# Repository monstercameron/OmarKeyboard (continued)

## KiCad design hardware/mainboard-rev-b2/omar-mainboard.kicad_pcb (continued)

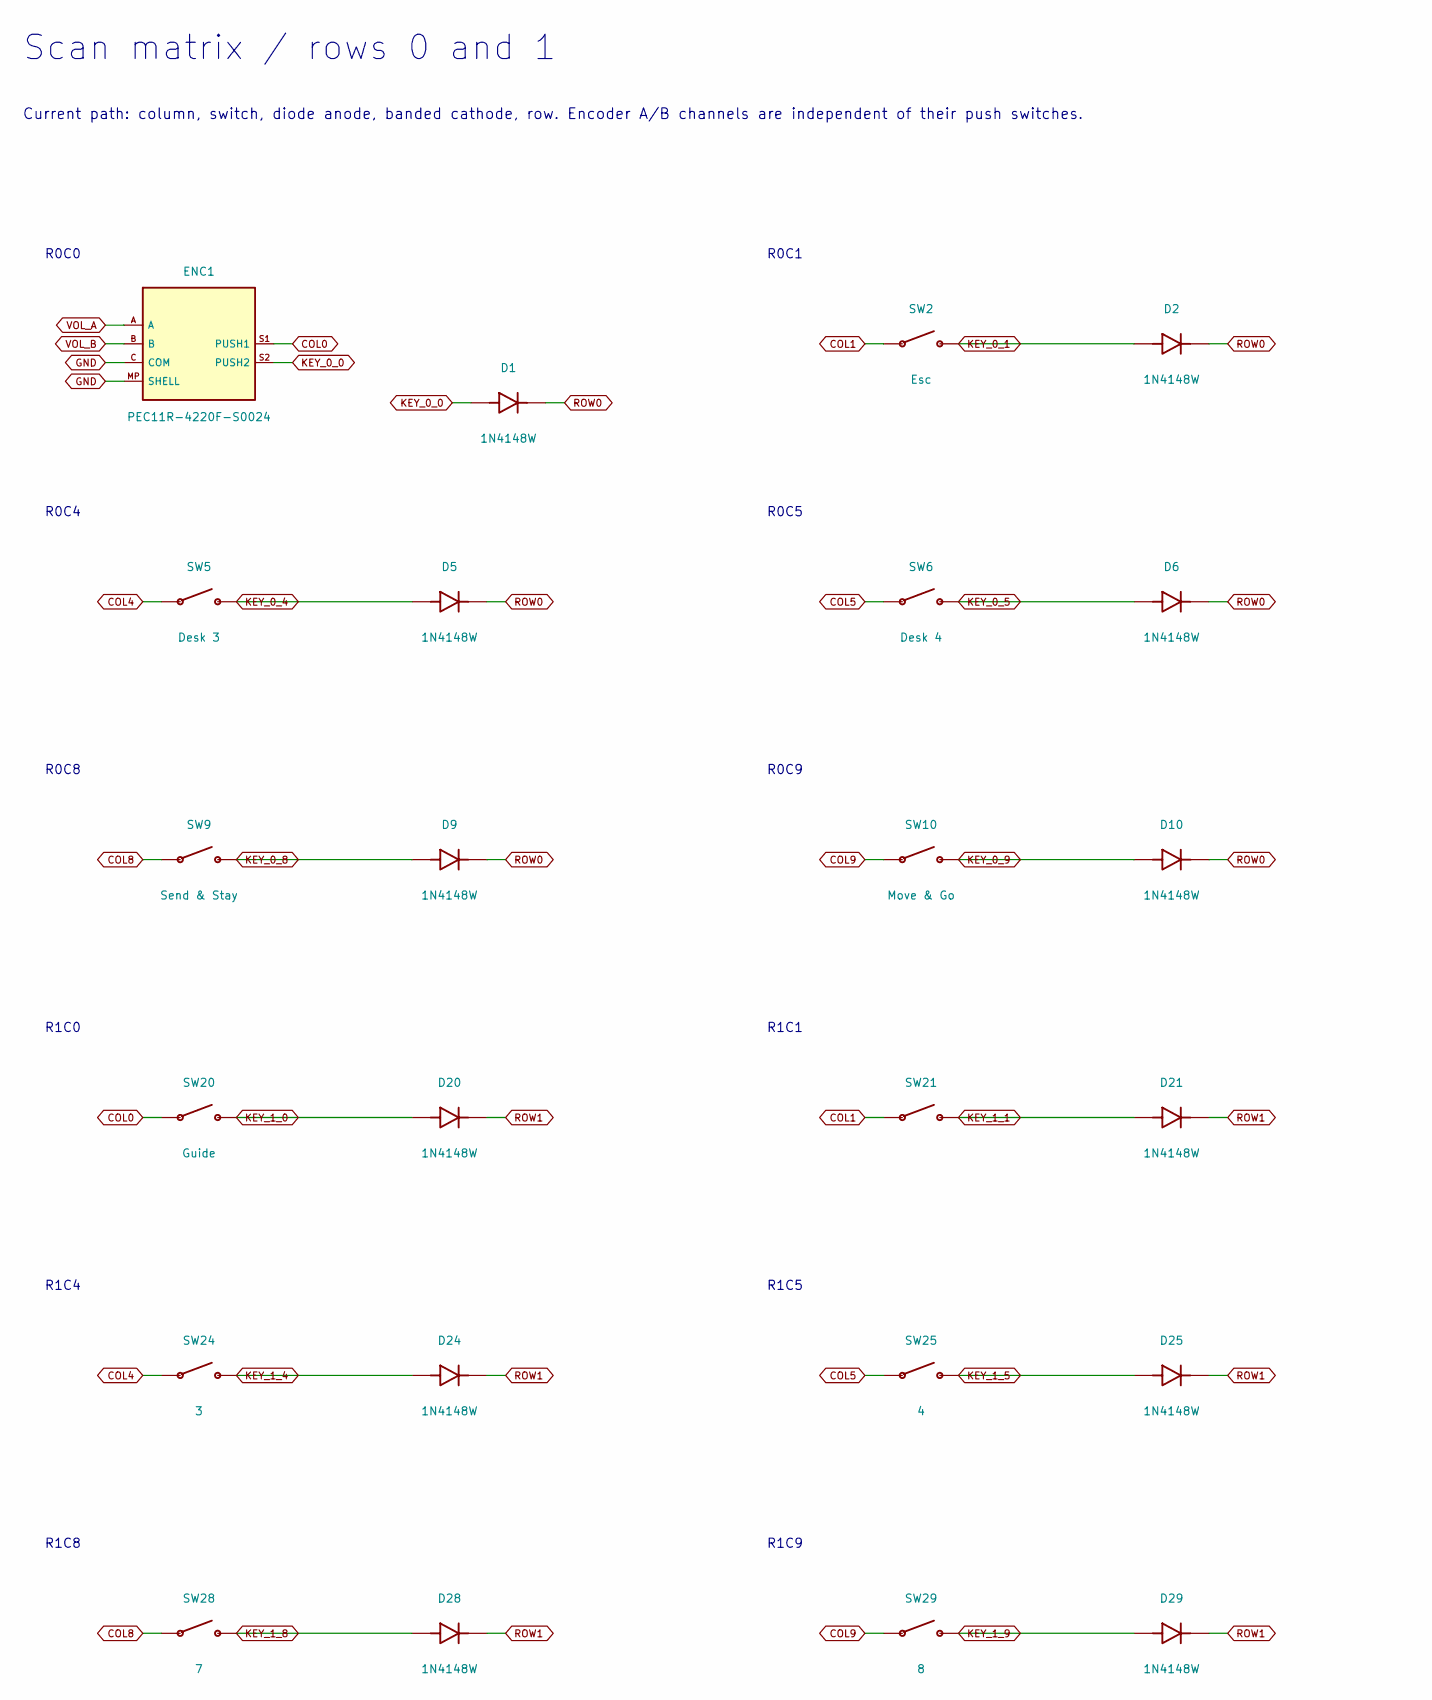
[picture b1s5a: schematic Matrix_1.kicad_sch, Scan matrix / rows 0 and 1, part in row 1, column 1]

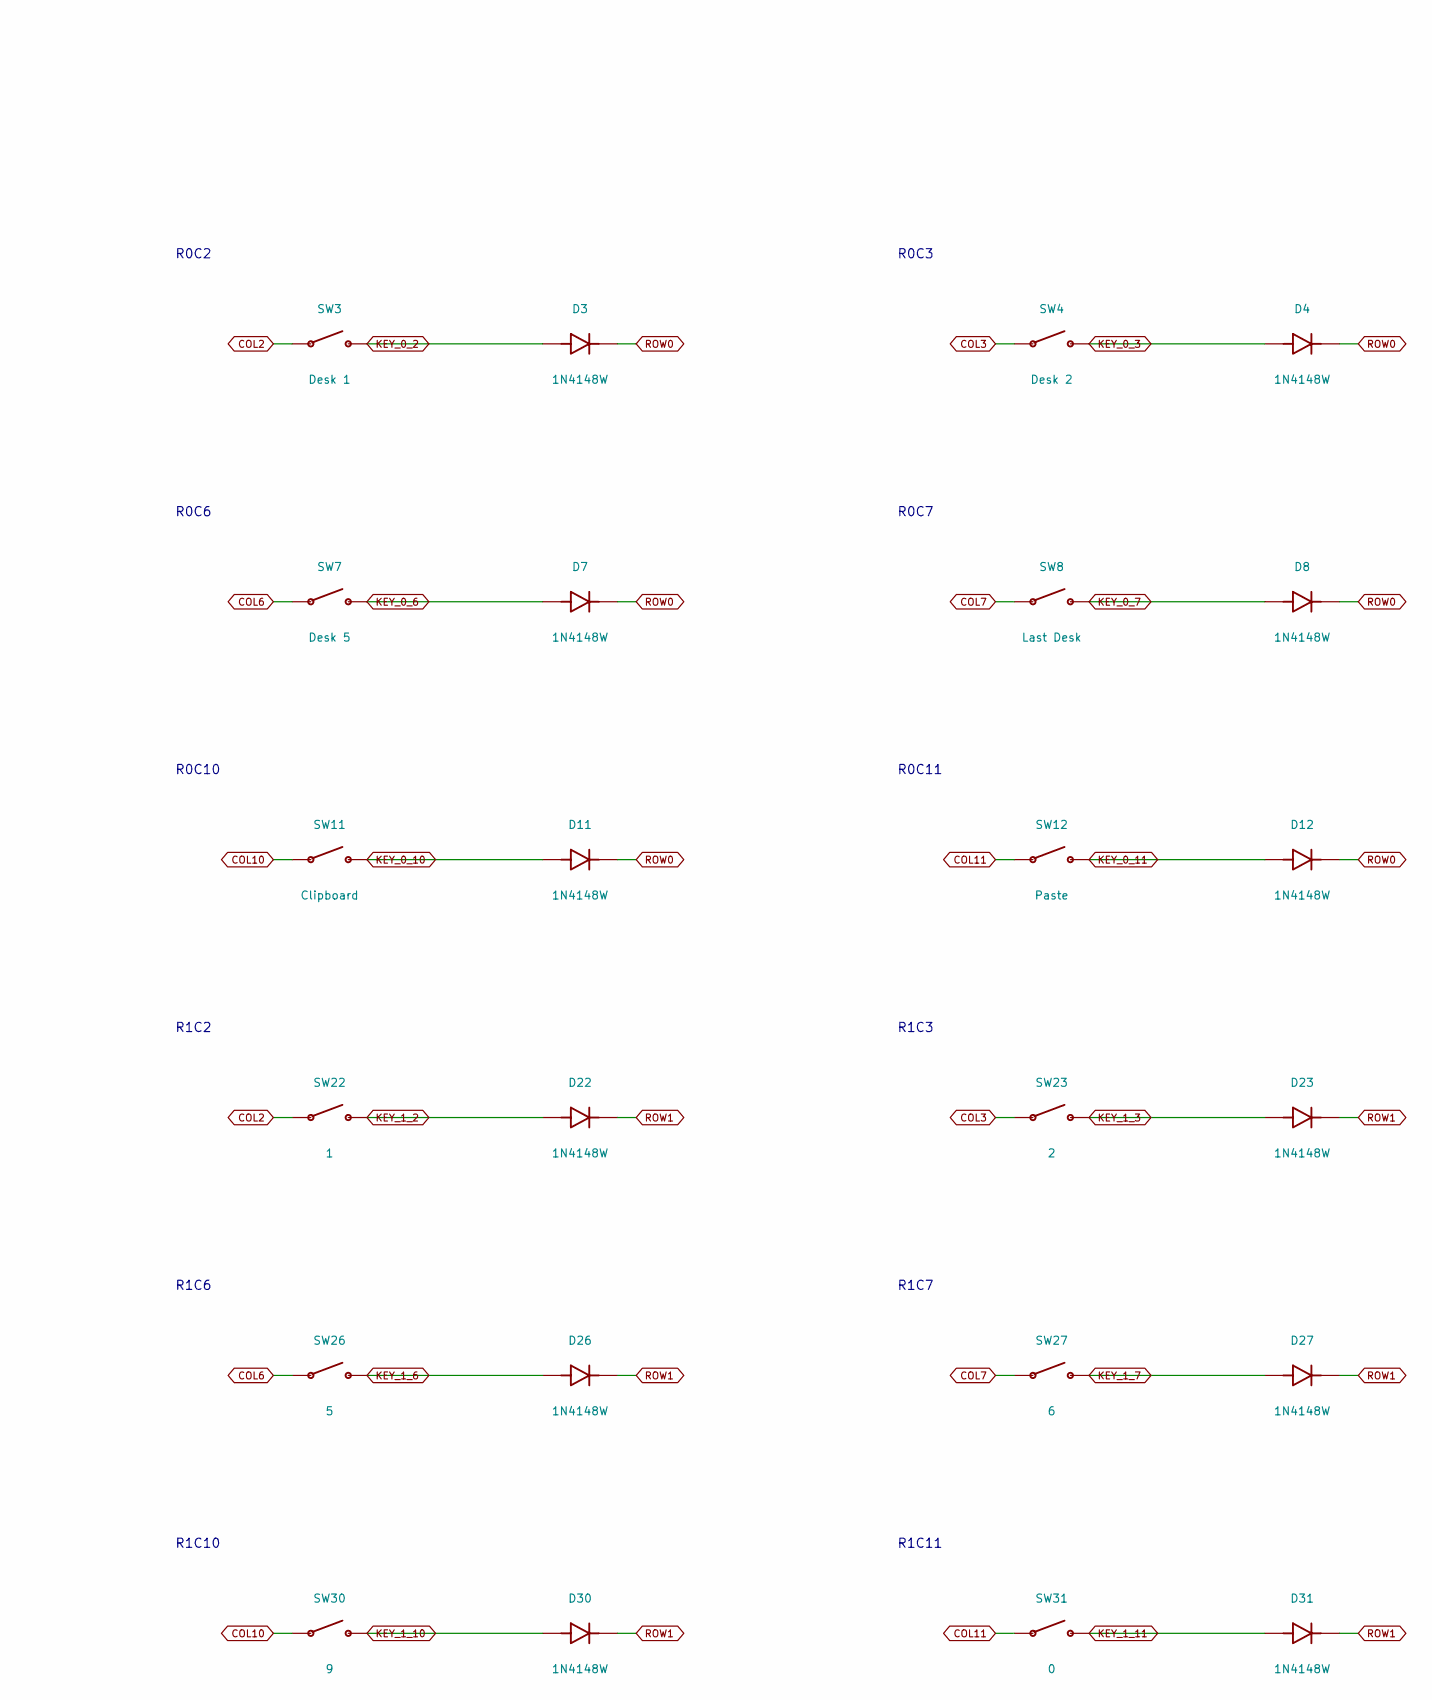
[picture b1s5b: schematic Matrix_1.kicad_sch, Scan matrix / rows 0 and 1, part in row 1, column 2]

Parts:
D1, D2, D3, D4, D5, D6, D7, D8, D9, D10, D11, D12, D20, D21, D22, D23, D24, D25, D26, D27, D28, D29, D30, D31: 1N4148W; D_SOD-123
ENC1: PEC11R-4220F-S0024; PEC11R_4xxxF_S
SW2: Esc; MX_Hotswap_North
SW3: Desk 1; MX_Hotswap_North
SW4: Desk 2; MX_Hotswap_North
SW5: Desk 3; MX_Hotswap_North
SW6: Desk 4; MX_Hotswap_North
SW7: Desk 5; MX_Hotswap_North
SW8: Last Desk; MX_Hotswap_North
SW9: Send & Stay; MX_Hotswap_North
SW10: Move & Go; MX_Hotswap_North
SW11: Clipboard; MX_Hotswap_North
SW12: Paste; MX_Hotswap_North
SW20: Guide; MX_Hotswap_North
SW21: MX_Hotswap_North
SW22: 1; MX_Hotswap_North
SW23: 2; MX_Hotswap_North
SW24: 3; MX_Hotswap_North
SW25: 4; MX_Hotswap_North
SW26: 5; MX_Hotswap_North
SW27: 6; MX_Hotswap_North
SW28: 7; MX_Hotswap_North
SW29: 8; MX_Hotswap_North
SW30: 9; MX_Hotswap_North
SW31: 0; MX_Hotswap_North

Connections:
COL0: ENC1.S1 (PUSH1), SW20.1; also elsewhere on the board
COL1: SW2.1, SW21.1; also elsewhere on the board
COL2: SW3.1, SW22.1; also elsewhere on the board
COL3: SW4.1, SW23.1; also elsewhere on the board
COL4: SW5.1, SW24.1; also elsewhere on the board
COL5: SW6.1, SW25.1; also elsewhere on the board
COL6: SW7.1, SW26.1; also elsewhere on the board
COL7: SW8.1, SW27.1; also elsewhere on the board
COL8: SW9.1, SW28.1; also elsewhere on the board
COL9: SW10.1, SW29.1; also elsewhere on the board
COL10: SW11.1, SW30.1; also elsewhere on the board
COL11: SW12.1, SW31.1; also elsewhere on the board
GND: ENC1.C (COM), ENC1.MP (SHELL); also elsewhere on the board
KEY_0_0: D1.2 (A), ENC1.S2 (PUSH2)
KEY_0_1: D2.2 (A), SW2.2
KEY_0_2: D3.2 (A), SW3.2
KEY_0_3: D4.2 (A), SW4.2
KEY_0_4: D5.2 (A), SW5.2
KEY_0_5: D6.2 (A), SW6.2
KEY_0_6: D7.2 (A), SW7.2
KEY_0_7: D8.2 (A), SW8.2
KEY_0_8: D9.2 (A), SW9.2
KEY_0_9: D10.2 (A), SW10.2
KEY_0_10: D11.2 (A), SW11.2
KEY_0_11: D12.2 (A), SW12.2
KEY_1_0: D20.2 (A), SW20.2
KEY_1_1: D21.2 (A), SW21.2
KEY_1_2: D22.2 (A), SW22.2
KEY_1_3: D23.2 (A), SW23.2
KEY_1_4: D24.2 (A), SW24.2
KEY_1_5: D25.2 (A), SW25.2
KEY_1_6: D26.2 (A), SW26.2
KEY_1_7: D27.2 (A), SW27.2
KEY_1_8: D28.2 (A), SW28.2
KEY_1_9: D29.2 (A), SW29.2
KEY_1_10: D30.2 (A), SW30.2
KEY_1_11: D31.2 (A), SW31.2
ROW0: D1.1 (K), D2.1 (K), D3.1 (K), D4.1 (K), D5.1 (K), D6.1 (K), D7.1 (K), D8.1 (K), D9.1 (K), D10.1 (K), D11.1 (K), D12.1 (K); also elsewhere on the board
ROW1: D20.1 (K), D21.1 (K), D22.1 (K), D23.1 (K), D24.1 (K), D25.1 (K), D26.1 (K), D27.1 (K), D28.1 (K), D29.1 (K), D30.1 (K), D31.1 (K); also elsewhere on the board
VOL_A: ENC1.A; also elsewhere on the board
VOL_B: ENC1.B; also elsewhere on the board

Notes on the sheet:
Scan matrix / rows 0 and 1
Current path: column, switch, diode anode, banded cathode, row. Encoder A/B channels are independent of their push switches.
R0C0
R0C1
R0C2
R0C3
R0C4
R0C5
R0C6
R0C7
R0C8
R0C9
R0C10
R0C11
R1C0
R1C1
R1C2
R1C3
R1C4
R1C5
R1C6
R1C7
R1C8
R1C9
R1C10
R1C11

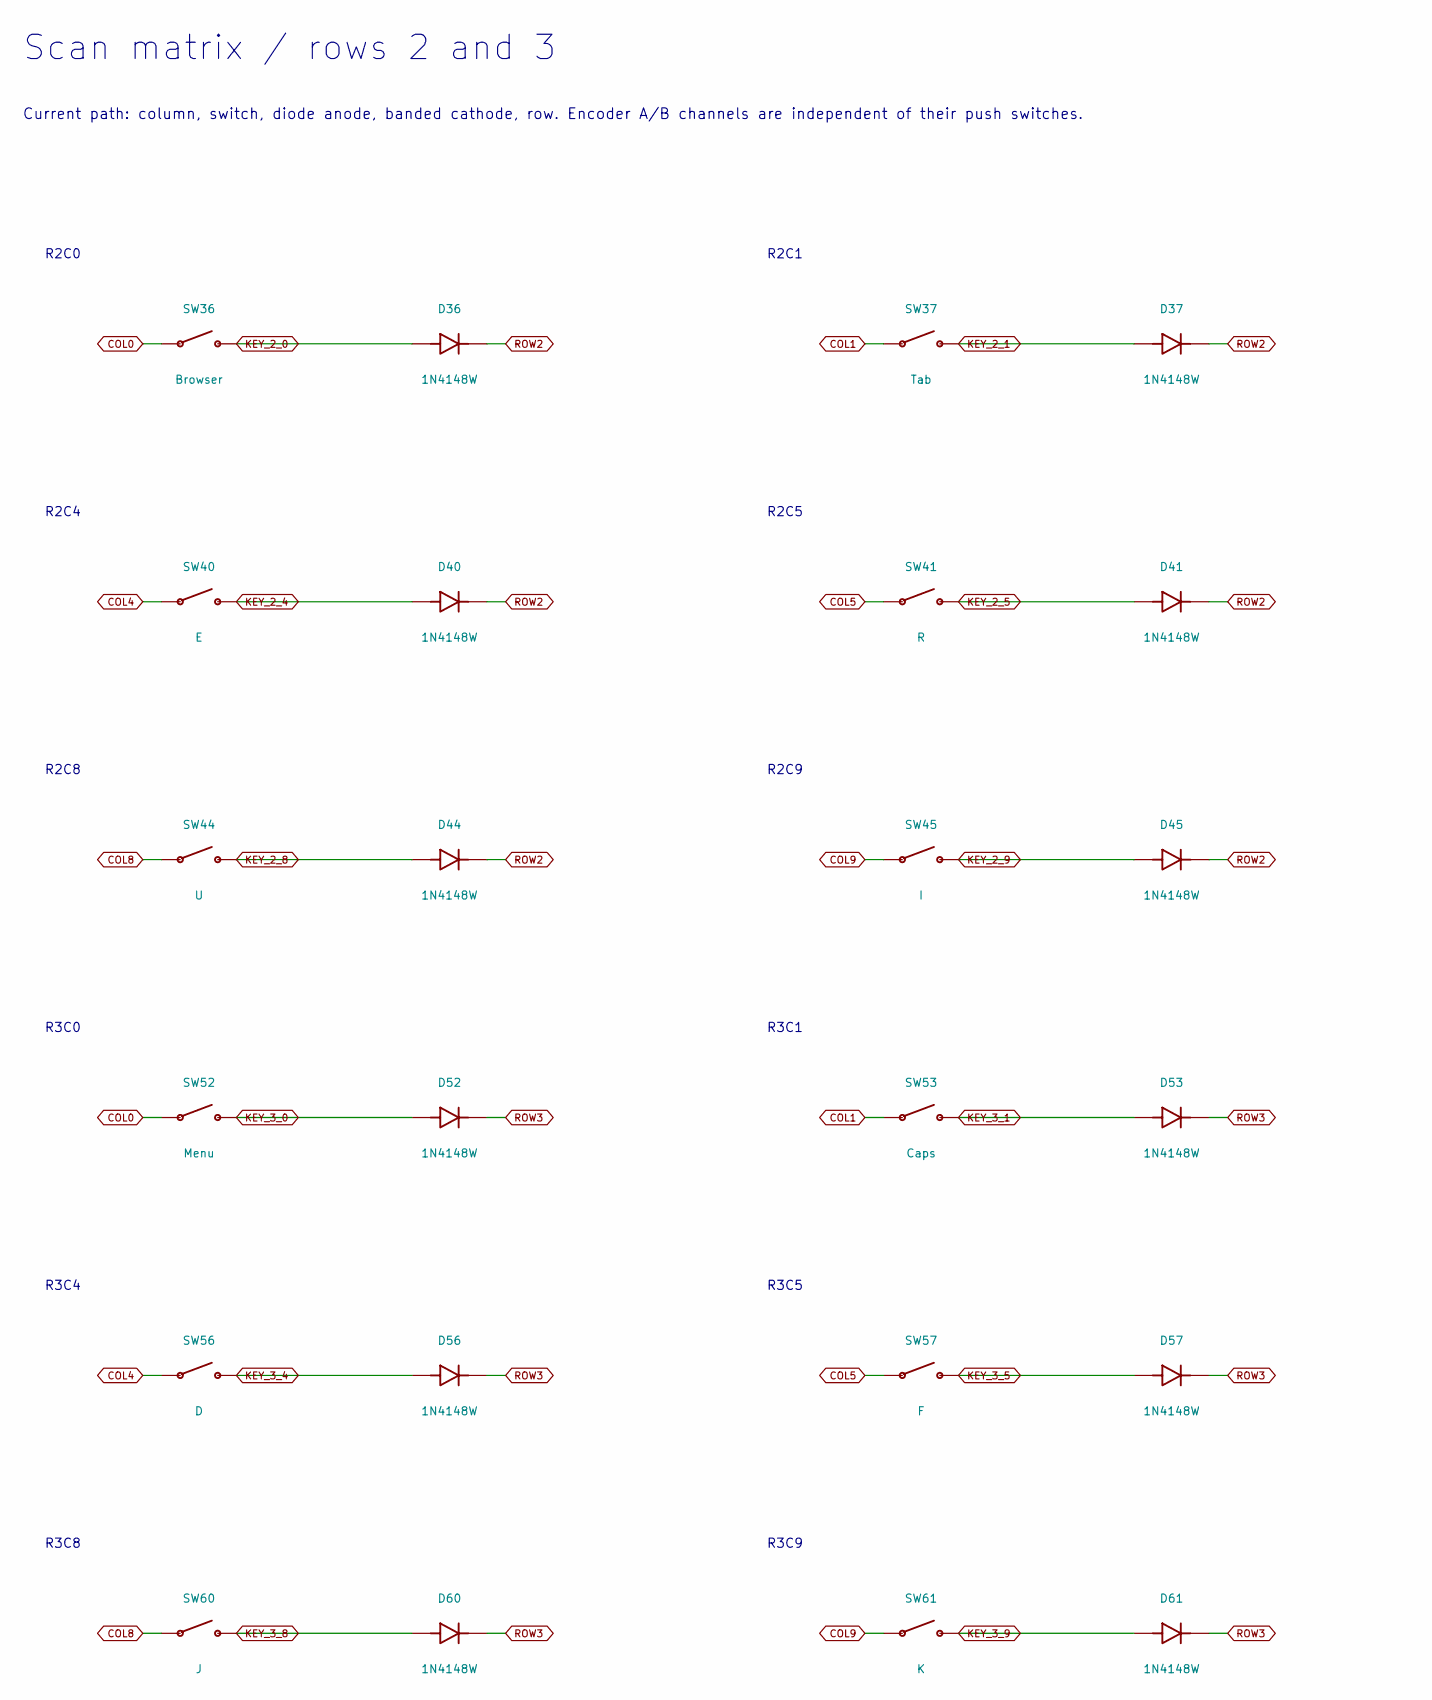
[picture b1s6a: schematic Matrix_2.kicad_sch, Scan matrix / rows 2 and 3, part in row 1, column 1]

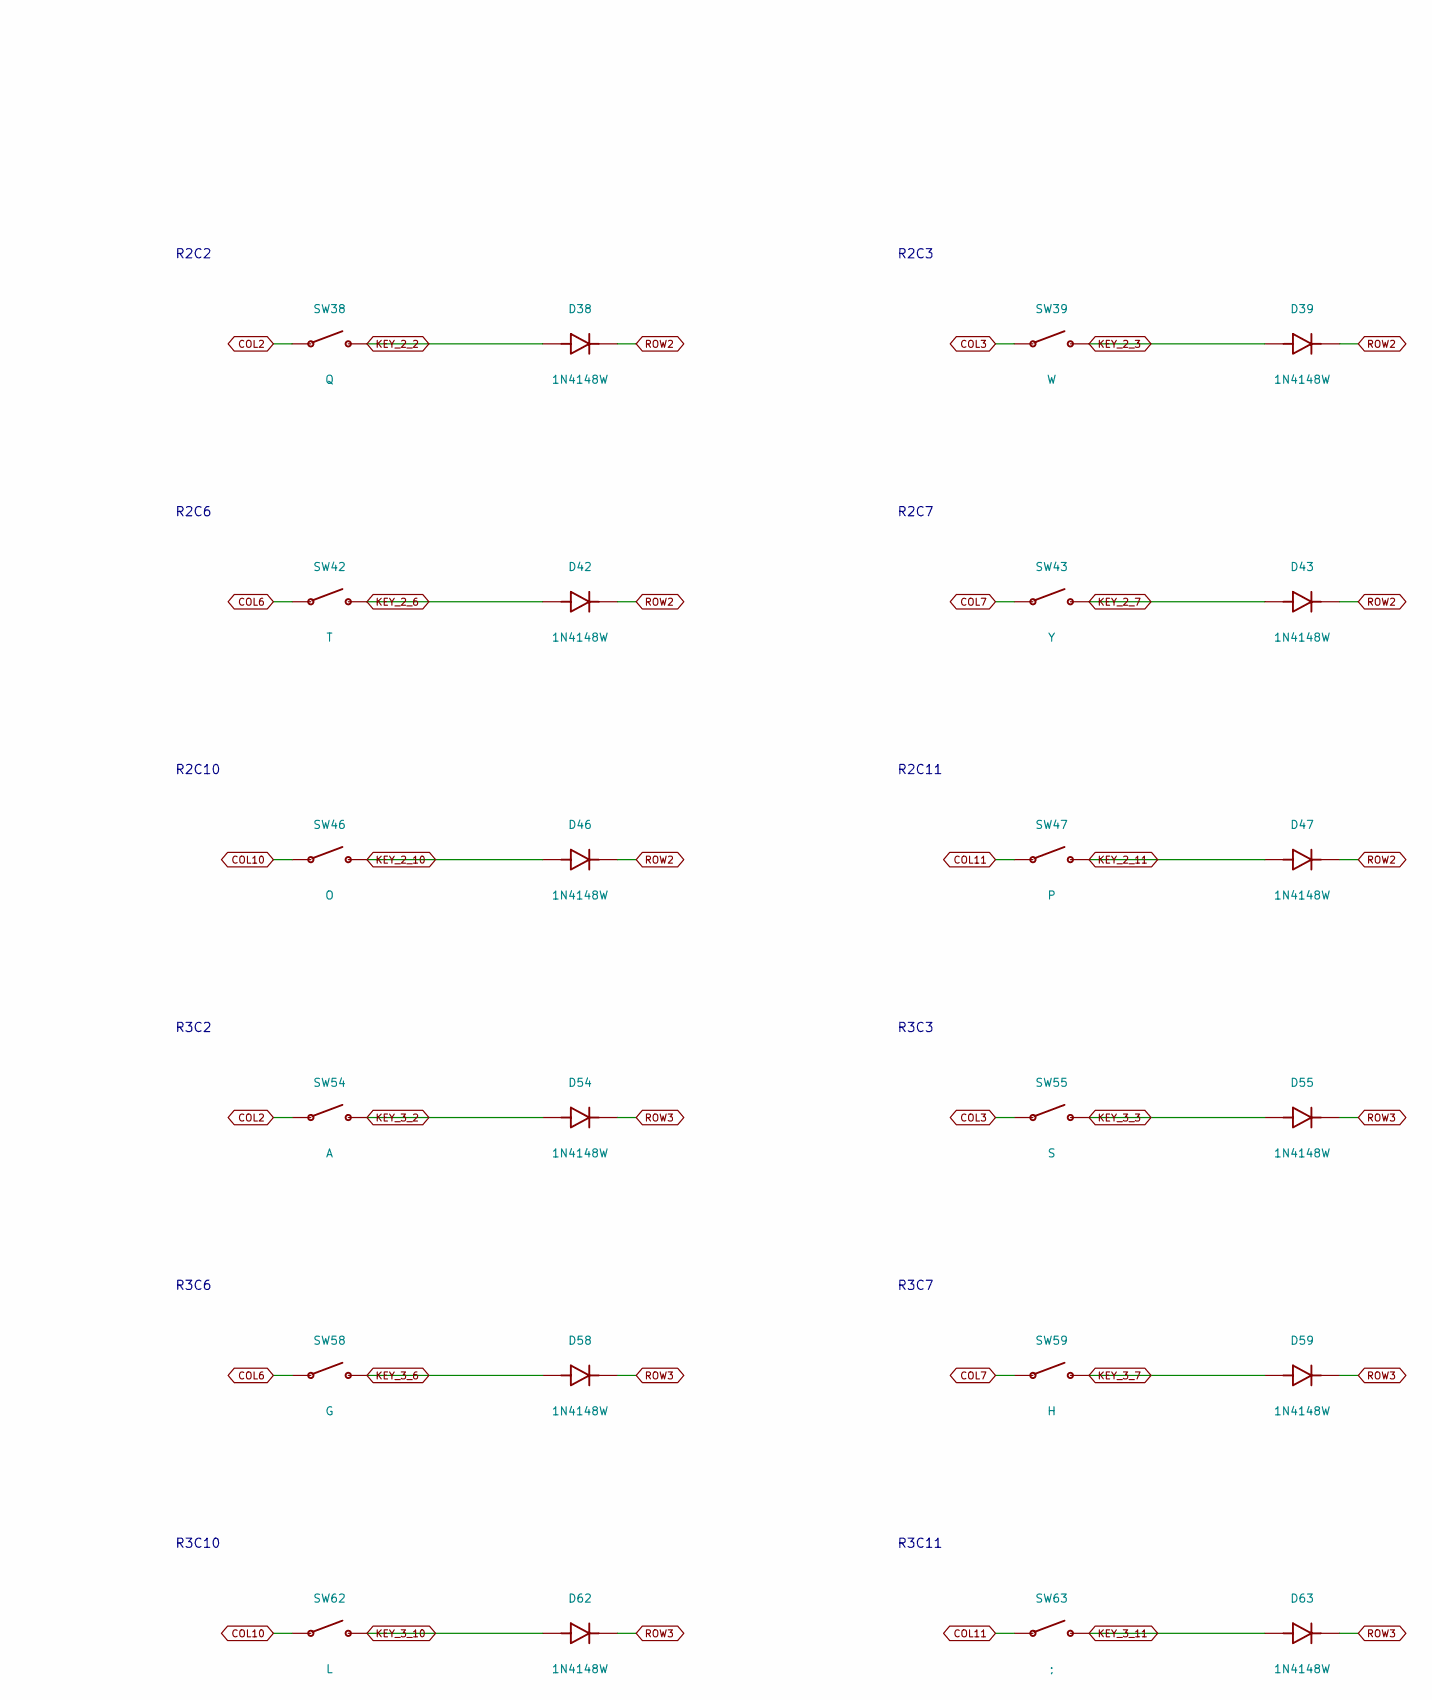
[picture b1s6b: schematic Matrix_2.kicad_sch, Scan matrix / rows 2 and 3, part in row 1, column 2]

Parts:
D36, D37, D38, D39, D40, D41, D42, D43, D44, D45, D46, D47, D52, D53, D54, D55, D56, D57, D58, D59, D60, D61, D62, D63: 1N4148W; D_SOD-123
SW36: Browser; MX_Hotswap_North
SW37: Tab; MX_Hotswap_North
SW38: Q; MX_Hotswap_North
SW39: W; MX_Hotswap_North
SW40: E; MX_Hotswap_North
SW41: R; MX_Hotswap_North
SW42: T; MX_Hotswap_North
SW43: Y; MX_Hotswap_North
SW44: U; MX_Hotswap_North
SW45: I; MX_Hotswap_North
SW46: O; MX_Hotswap_North
SW47: P; MX_Hotswap_North
SW52: Menu; MX_Hotswap_North
SW53: Caps; MX_Hotswap_North
SW54: A; MX_Hotswap_North
SW55: S; MX_Hotswap_North
SW56: D; MX_Hotswap_North
SW57: F; MX_Hotswap_North
SW58: G; MX_Hotswap_North
SW59: H; MX_Hotswap_North
SW60: J; MX_Hotswap_North
SW61: K; MX_Hotswap_North
SW62: L; MX_Hotswap_North
SW63: ;; MX_Hotswap_North

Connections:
COL0: SW36.1, SW52.1; also elsewhere on the board
COL1: SW37.1, SW53.1; also elsewhere on the board
COL2: SW38.1, SW54.1; also elsewhere on the board
COL3: SW39.1, SW55.1; also elsewhere on the board
COL4: SW40.1, SW56.1; also elsewhere on the board
COL5: SW41.1, SW57.1; also elsewhere on the board
COL6: SW42.1, SW58.1; also elsewhere on the board
COL7: SW43.1, SW59.1; also elsewhere on the board
COL8: SW44.1, SW60.1; also elsewhere on the board
COL9: SW45.1, SW61.1; also elsewhere on the board
COL10: SW46.1, SW62.1; also elsewhere on the board
COL11: SW47.1, SW63.1; also elsewhere on the board
KEY_2_0: D36.2 (A), SW36.2
KEY_2_1: D37.2 (A), SW37.2
KEY_2_2: D38.2 (A), SW38.2
KEY_2_3: D39.2 (A), SW39.2
KEY_2_4: D40.2 (A), SW40.2
KEY_2_5: D41.2 (A), SW41.2
KEY_2_6: D42.2 (A), SW42.2
KEY_2_7: D43.2 (A), SW43.2
KEY_2_8: D44.2 (A), SW44.2
KEY_2_9: D45.2 (A), SW45.2
KEY_2_10: D46.2 (A), SW46.2
KEY_2_11: D47.2 (A), SW47.2
KEY_3_0: D52.2 (A), SW52.2
KEY_3_1: D53.2 (A), SW53.2
KEY_3_2: D54.2 (A), SW54.2
KEY_3_3: D55.2 (A), SW55.2
KEY_3_4: D56.2 (A), SW56.2
KEY_3_5: D57.2 (A), SW57.2
KEY_3_6: D58.2 (A), SW58.2
KEY_3_7: D59.2 (A), SW59.2
KEY_3_8: D60.2 (A), SW60.2
KEY_3_9: D61.2 (A), SW61.2
KEY_3_10: D62.2 (A), SW62.2
KEY_3_11: D63.2 (A), SW63.2
ROW2: D36.1 (K), D37.1 (K), D38.1 (K), D39.1 (K), D40.1 (K), D41.1 (K), D42.1 (K), D43.1 (K), D44.1 (K), D45.1 (K), D46.1 (K), D47.1 (K); also elsewhere on the board
ROW3: D52.1 (K), D53.1 (K), D54.1 (K), D55.1 (K), D56.1 (K), D57.1 (K), D58.1 (K), D59.1 (K), D60.1 (K), D61.1 (K), D62.1 (K), D63.1 (K); also elsewhere on the board

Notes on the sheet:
Scan matrix / rows 2 and 3
Current path: column, switch, diode anode, banded cathode, row. Encoder A/B channels are independent of their push switches.
R2C0
R2C1
R2C2
R2C3
R2C4
R2C5
R2C6
R2C7
R2C8
R2C9
R2C10
R2C11
R3C0
R3C1
R3C2
R3C3
R3C4
R3C5
R3C6
R3C7
R3C8
R3C9
R3C10
R3C11

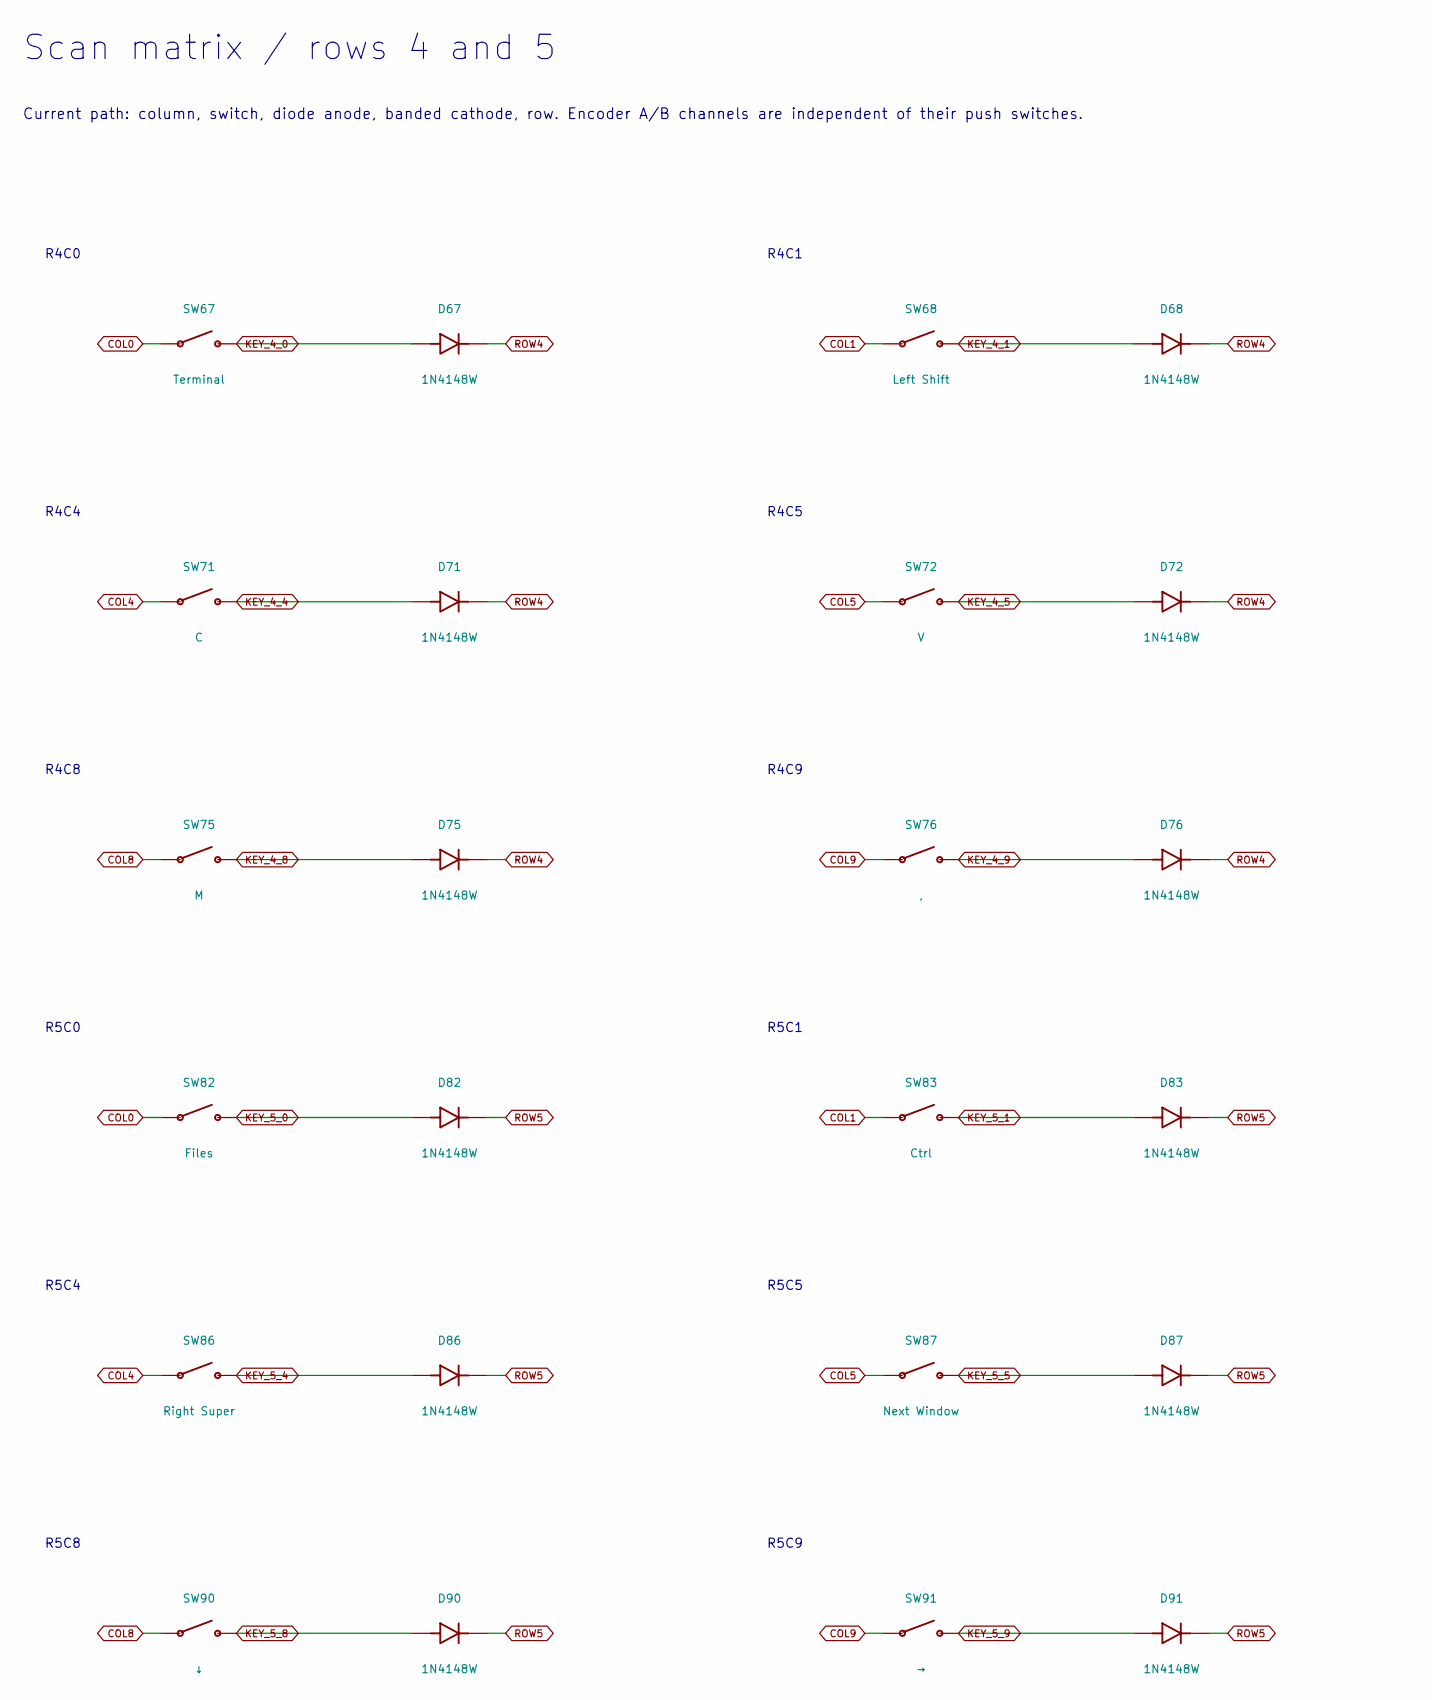
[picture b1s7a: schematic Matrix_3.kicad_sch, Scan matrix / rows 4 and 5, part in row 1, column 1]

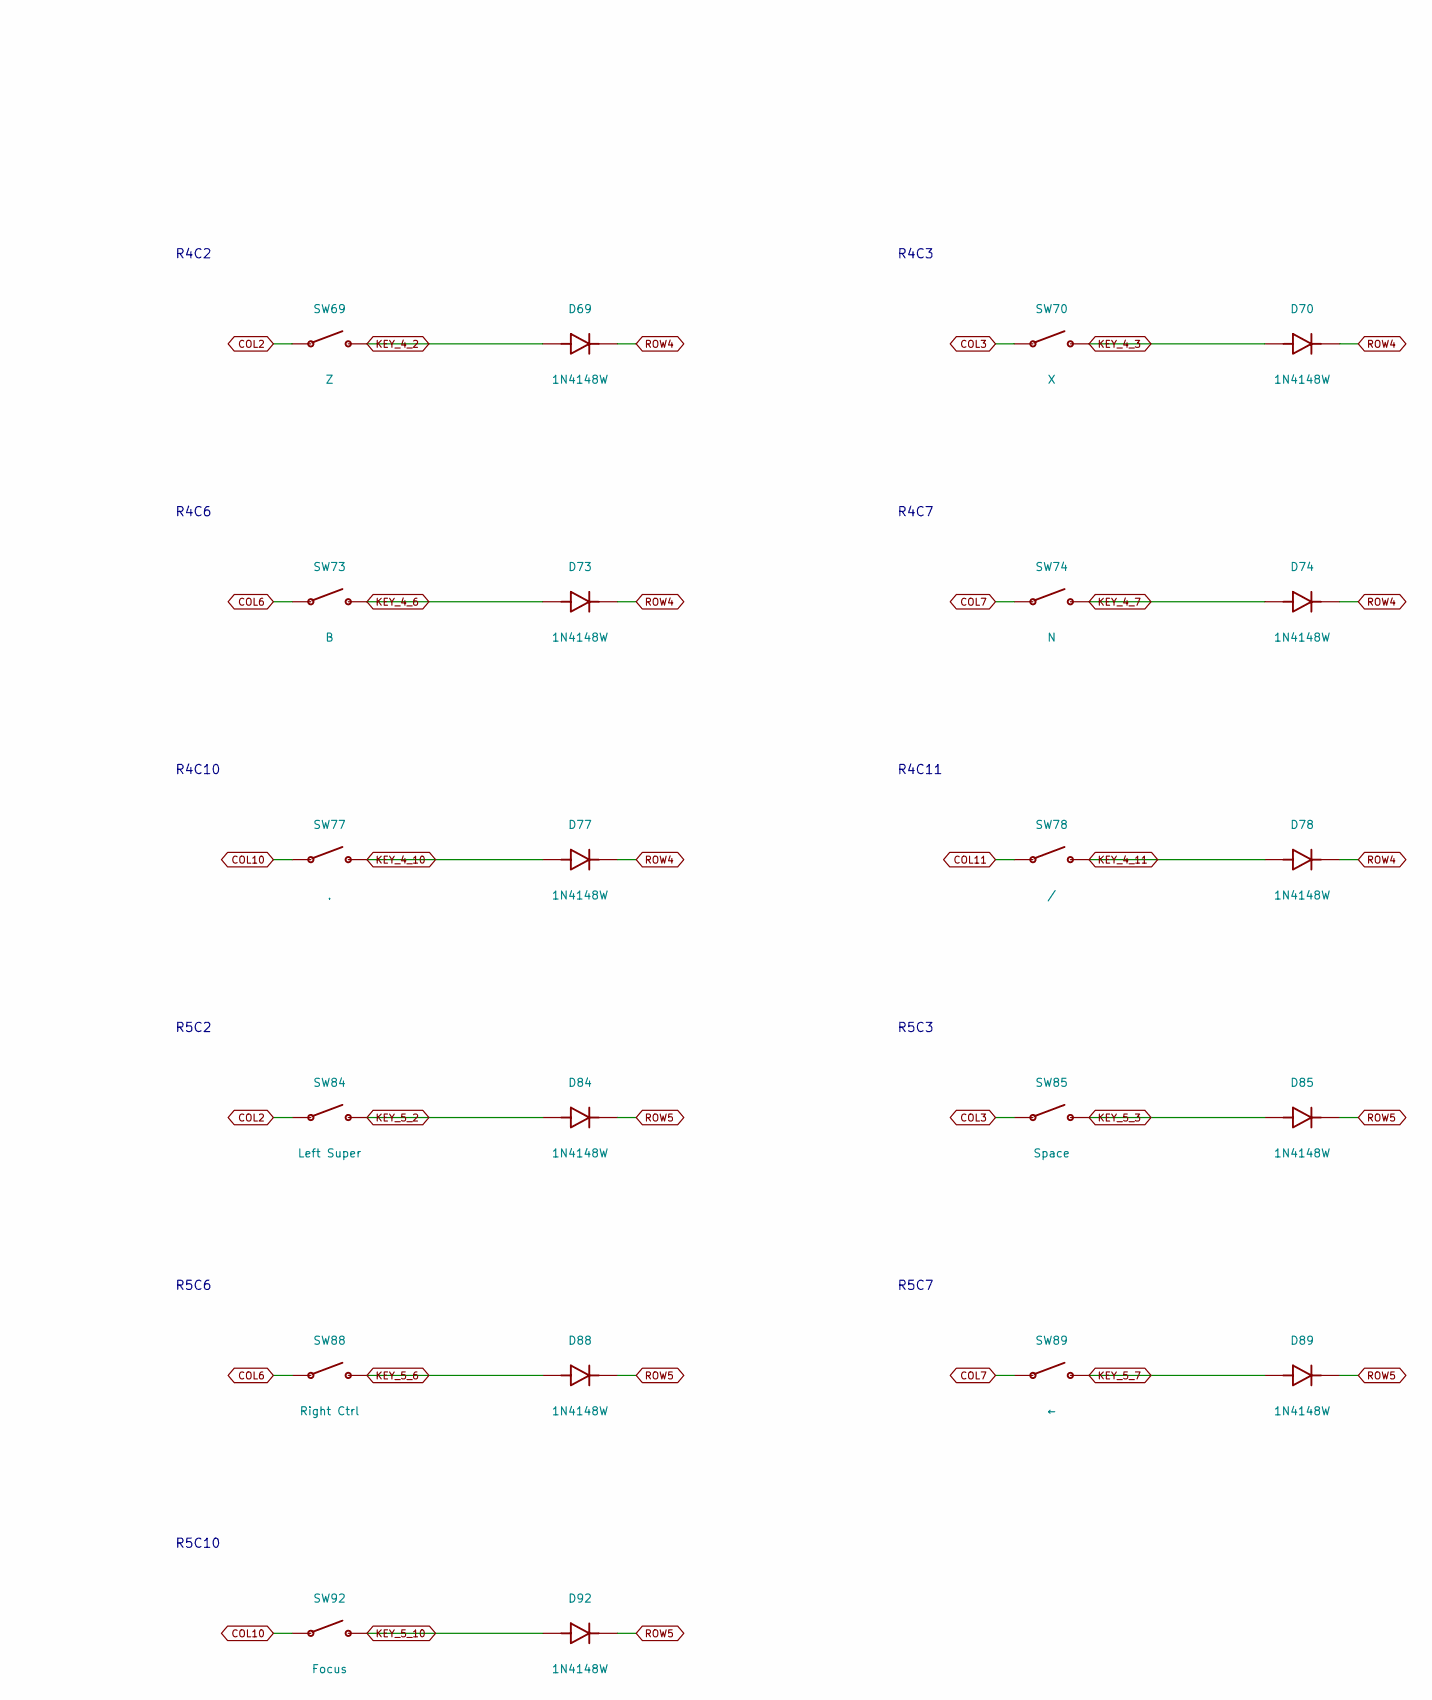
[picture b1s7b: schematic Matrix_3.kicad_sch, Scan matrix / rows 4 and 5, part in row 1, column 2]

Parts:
D67, D68, D69, D70, D71, D72, D73, D74, D76, D77, D78, D82, D83, D84, D85, D86, D87, D88, D89, D90, D91, D92: 1N4148W; D_SOD-123
D75: 1N4148W; D_SOD123_Stabilizer_Clearance
SW67: Terminal; MX_Hotswap_North
SW68: Left Shift; MX_Hotswap_North
SW69: Z; MX_Hotswap_North
SW70: X; MX_Hotswap_North
SW71: C; MX_Hotswap_North
SW72: V; MX_Hotswap_North
SW73: B; MX_Hotswap_North
SW74: N; MX_Hotswap_North
SW75: M; MX_Hotswap_North
SW76: ,; MX_Hotswap_North
SW77: .; MX_Hotswap_North
SW78: /; MX_Hotswap_North
SW82: Files; MX_Hotswap_North
SW83: Ctrl; MX_Hotswap_North
SW84: Left Super; MX_Hotswap_North
SW85: Space; MX_Hotswap_North
SW86: Right Super; MX_Hotswap_North
SW87: Next Window; MX_Hotswap_North
SW88: Right Ctrl; MX_Hotswap_North
SW89: ←; MX_Hotswap_North
SW90: ↓; MX_Hotswap_North
SW91: →; MX_Hotswap_North
SW92: Focus; MX_Hotswap_North

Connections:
COL0: SW67.1, SW82.1; also elsewhere on the board
COL1: SW68.1, SW83.1; also elsewhere on the board
COL2: SW69.1, SW84.1; also elsewhere on the board
COL3: SW70.1, SW85.1; also elsewhere on the board
COL4: SW71.1, SW86.1; also elsewhere on the board
COL5: SW72.1, SW87.1; also elsewhere on the board
COL6: SW73.1, SW88.1; also elsewhere on the board
COL7: SW74.1, SW89.1; also elsewhere on the board
COL8: SW75.1, SW90.1; also elsewhere on the board
COL9: SW76.1, SW91.1; also elsewhere on the board
COL10: SW77.1, SW92.1; also elsewhere on the board
COL11: SW78.1; also elsewhere on the board
KEY_4_0: D67.2 (A), SW67.2
KEY_4_1: D68.2 (A), SW68.2
KEY_4_2: D69.2 (A), SW69.2
KEY_4_3: D70.2 (A), SW70.2
KEY_4_4: D71.2 (A), SW71.2
KEY_4_5: D72.2 (A), SW72.2
KEY_4_6: D73.2 (A), SW73.2
KEY_4_7: D74.2 (A), SW74.2
KEY_4_8: D75.2 (A), SW75.2
KEY_4_9: D76.2 (A), SW76.2
KEY_4_10: D77.2 (A), SW77.2
KEY_4_11: D78.2 (A), SW78.2
KEY_5_0: D82.2 (A), SW82.2
KEY_5_1: D83.2 (A), SW83.2
KEY_5_2: D84.2 (A), SW84.2
KEY_5_3: D85.2 (A), SW85.2
KEY_5_4: D86.2 (A), SW86.2
KEY_5_5: D87.2 (A), SW87.2
KEY_5_6: D88.2 (A), SW88.2
KEY_5_7: D89.2 (A), SW89.2
KEY_5_8: D90.2 (A), SW90.2
KEY_5_9: D91.2 (A), SW91.2
KEY_5_10: D92.2 (A), SW92.2
ROW4: D67.1 (K), D68.1 (K), D69.1 (K), D70.1 (K), D71.1 (K), D72.1 (K), D73.1 (K), D74.1 (K), D75.1 (K), D76.1 (K), D77.1 (K), D78.1 (K); also elsewhere on the board
ROW5: D82.1 (K), D83.1 (K), D84.1 (K), D85.1 (K), D86.1 (K), D87.1 (K), D88.1 (K), D89.1 (K), D90.1 (K), D91.1 (K), D92.1 (K); also elsewhere on the board

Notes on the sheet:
Scan matrix / rows 4 and 5
Current path: column, switch, diode anode, banded cathode, row. Encoder A/B channels are independent of their push switches.
R4C0
R4C1
R4C2
R4C3
R4C4
R4C5
R4C6
R4C7
R4C8
R4C9
R4C10
R4C11
R5C0
R5C1
R5C2
R5C3
R5C4
R5C5
R5C6
R5C7
R5C8
R5C9
R5C10
